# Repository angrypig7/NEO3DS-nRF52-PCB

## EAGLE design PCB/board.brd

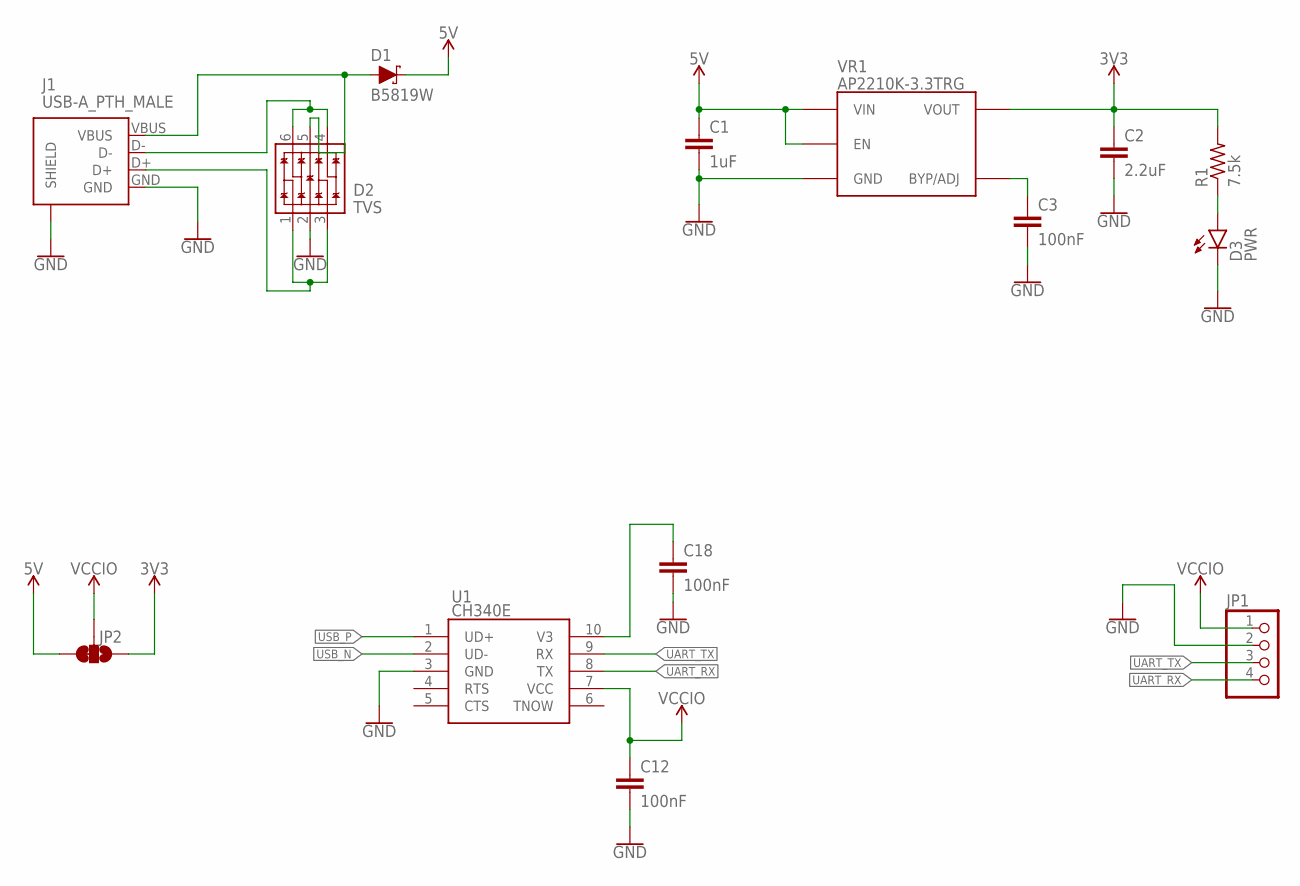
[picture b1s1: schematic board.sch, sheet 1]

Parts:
C1: 1uF; C0402; LCSC C52923
C2: 2.2uF; C0603; LCSC C23630
C3, C12, C18: 100nF; C0402; LCSC C1525
D1: B5819W; SOD-123; LCSC C8598
D2: TVS; SPT-23-6; LCSC C85364
D3: PWR; LED_0603; LCSC C72038
J1: USB-A_PTH_MALE; USB-A-MALE-H-PTH-1; LCSC C9739
JP1: Rx Tx G V; 1X04-NOSILK
JP2: 5V 3V3; SMT-JUMPER_3_1-NC_TRACE_NO-SILK
R1: 7.5k; R0402; LCSC C25918
U1: CH340E; MSOP-10; LCSC C99652
VR1: AP2210K-3.3TRG; SOT-23-5; LCSC C176959

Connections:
3V3: C2.1, JP2.1, R1.2, VR1.5 (VOUT); also elsewhere on the board
5V: C1.1, D1.C, JP2.3, VR1.1 (VIN), VR1.3 (EN)
GND: C1.2, C2.2, C3.2, C12.2, C18.2, D2.2 (VSS), D3.C, J1.GND, J1.SHIELD@0 (SHIELD), J1.SHIELD@1 (SHIELD), J1.SHIELD@2 (SHIELD), J1.SHIELD@3 (SHIELD), JP1.2, U1.3 (GND), VR1.2 (GND); also elsewhere on the board
unnamed: C3.1, VR1.4 (BYP/ADJ)
unnamed: D3.A, R1.1
unnamed: C18.1, U1.10 (V3)
UART_RX: JP1.4, U1.8 (TX); also elsewhere on the board
UART_TX: JP1.3, U1.9 (RX); also elsewhere on the board
USB_IN: D1.A, D2.5 (VCC), J1.VBUS
USB_N: D2.4 (IO3), D2.6 (IO4), J1.D-, U1.2 (UD-)
USB_P: D2.1 (IO1), D2.3 (IO2), J1.D+, U1.1 (UD+)
VCCIO: C12.1, JP1.1, JP2.2, U1.7 (VCC)

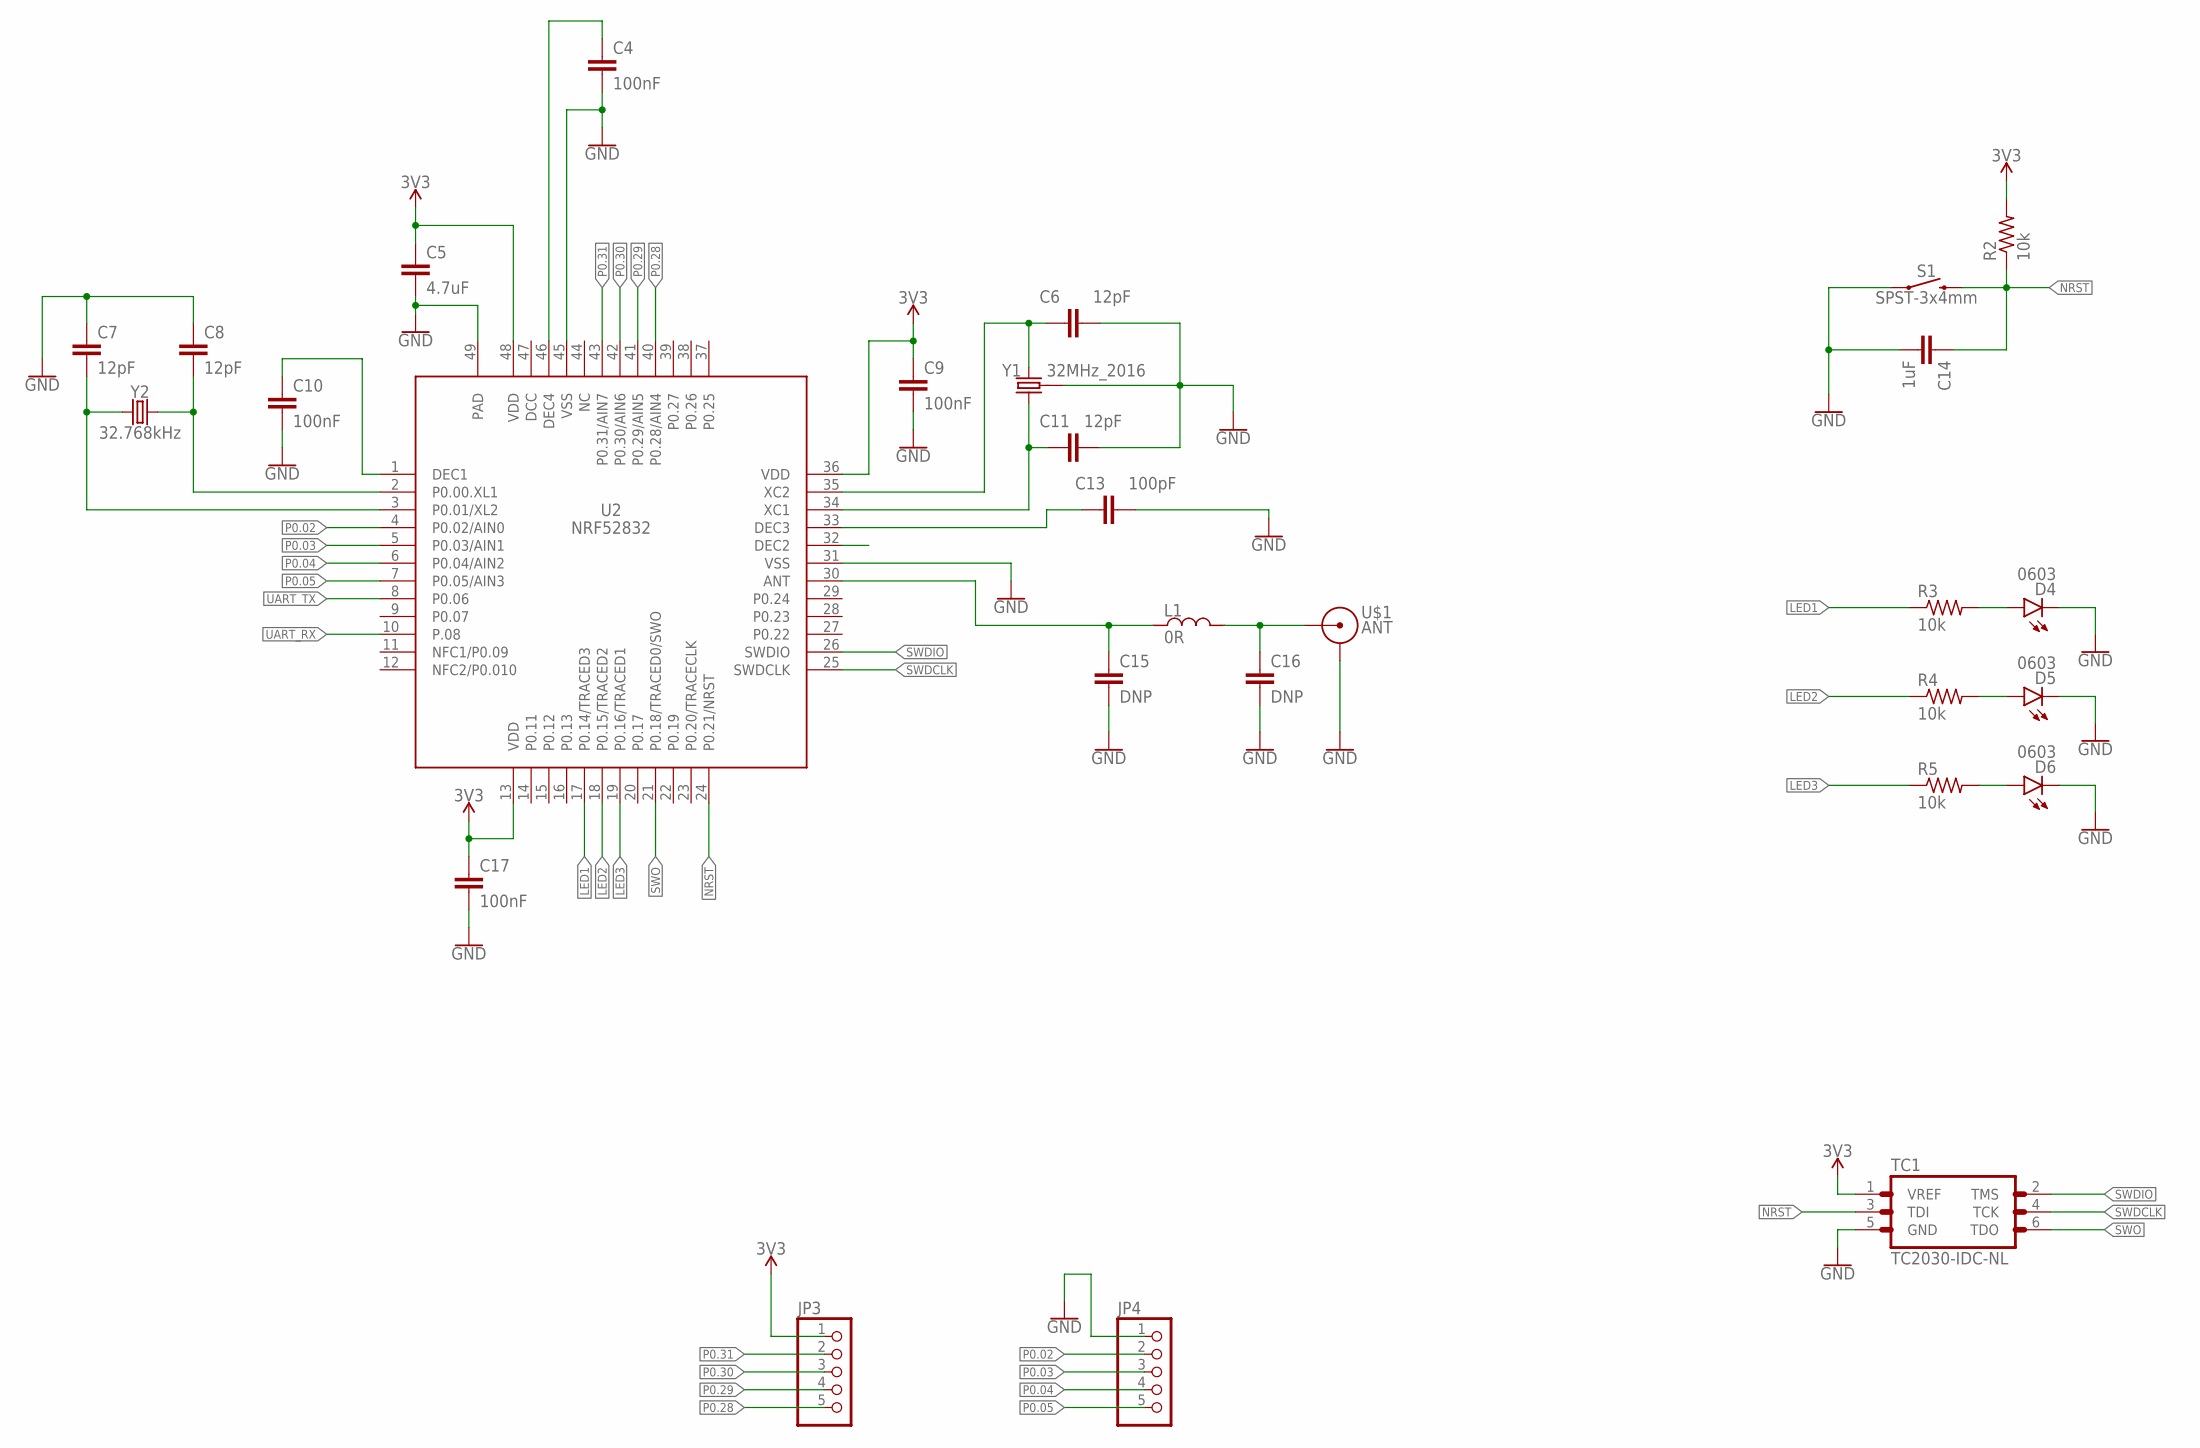
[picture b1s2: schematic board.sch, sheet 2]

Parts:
C4, C9, C10, C17: 100nF; C0402; LCSC C1525
C5: 4.7uF; C0402; LCSC C23733
C6, C7, C8, C11: 12pF; C0402; LCSC C1547
C13: 100pF; C0402; LCSC C1546
C14: 1uF; C0402; LCSC C52923
C15, C16: DNP; C0402
D4, D5, D6: 0603; LED_0603; LCSC C2286
JP3, JP4: PINHD-1X5-NOSILK; 1X05-NOSILK
L1: 0R; R0402; LCSC C17168
R2, R3, R4, R5: 10k; R0402; LCSC C25744
S1: SPST-3x4mm; TACTILE_SWITCH_SMD_3.0X4.0MM; LCSC C720477
TC1: TC2030-IDC-NL
U2: NRF52832; QFN40P600X600X90-49T450N; JLC_ROTATION 270
U$1: ANT; TI-AN043_LEFT_SHORTER
Y1: 32MHz_2016; CRYSTAL-SMD-2.0X1.6MM; LCSC C255896
Y2: 32.768kHz; CRYSTAL-SMD-3.2X1.5MM; LCSC C32346

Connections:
3V3: C5.1, C9.1, C17.1, JP3.1, R2.2, TC1.1 (VREF), U2.13 (VDD), U2.36 (VDD), U2.48 (VDD); also elsewhere on the board
GND: C4.2, C5.2, C6.2, C7.1, C8.1, C9.2, C10.2, C11.2, C13.2, C14.2, C15.2, C16.2, C17.2, D4.C, D5.C, D6.C, JP4.1, S1.1, TC1.5 (GND), U2.31 (VSS), U2.45 (VSS), U2.49 (PAD), U$1.GND, Y1.2 (GND), Y1.4 (GND); also elsewhere on the board
LED1: R3.1, U2.17 (P0.14/TRACED3)
LED2: R4.1, U2.18 (P0.15/TRACED2)
LED3: R5.1, U2.19 (P0.16/TRACED1)
unnamed: C8.2, U2.2 (P0.00.XL1), Y2.P$2 (2)
unnamed: D4.A, R3.2
unnamed: C7.2, U2.3 (P0.01/XL2), Y2.P$1 (1)
unnamed: C10.1, U2.1 (DEC1)
unnamed: C4.1, U2.46 (DEC4)
unnamed: C6.1, U2.35 (XC2), Y1.3 (2)
unnamed: C11.1, U2.34 (XC1), Y1.1
unnamed: C13.1, U2.33 (DEC3)
unnamed: D5.A, R4.2
unnamed: D6.A, R5.2
NRST: C14.1, R2.1, S1.2, TC1.3 (TDI), U2.24 (P0.21/NRST)
P0.02: JP4.2, U2.4 (P0.02/AIN0)
P0.03: JP4.3, U2.5 (P0.03/AIN1)
P0.04: JP4.4, U2.6 (P0.04/AIN2)
P0.05: JP4.5, U2.7 (P0.05/AIN3)
P0.28: JP3.5, U2.40 (P0.28/AIN4)
P0.29: JP3.4, U2.41 (P0.29/AIN5)
P0.30: JP3.3, U2.42 (P0.30/AIN6)
P0.31: JP3.2, U2.43 (P0.31/AIN7)
RF-1: C15.1, L1.1, U2.30 (ANT)
RF-2: C16.1, L1.2, U$1.RF (FEED)
SWDCLK: TC1.4 (TCK), U2.25 (SWDCLK)
SWDIO: TC1.2 (TMS), U2.26 (SWDIO)
SWO: TC1.6 (TDO), U2.21 (P0.18/TRACED0/SWO)
UART_RX: U2.10 (P.08); also elsewhere on the board
UART_TX: U2.8 (P0.06); also elsewhere on the board

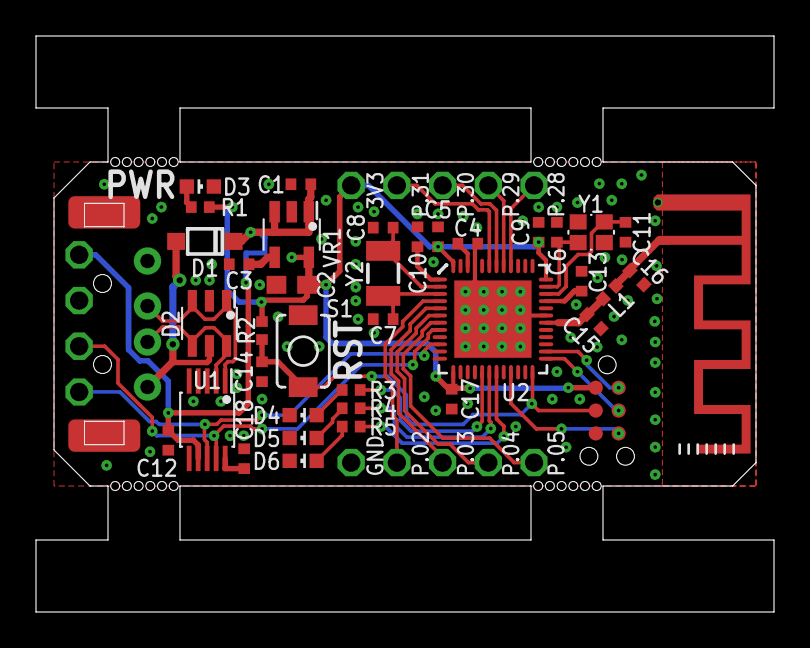
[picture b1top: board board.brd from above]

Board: 2 copper layers, 41.0 x 32.0 mm, 43 parts (1 on the bottom side), 39 nets.

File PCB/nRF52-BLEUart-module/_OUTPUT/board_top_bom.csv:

Comment,Designator,Footprint,LCSC Part #
0R,L1,R0402,C17168
1uF,C1 C14,C0402,C52923
2.2uF,C2,C0603,C23630
4.7uF,C5,C0402,C23733
7.5k,R1,R0402,C25918
10k,R2 R3 R4 R5,R0402,C25744
12pF,C6 C7 C8 C11,C0402,C1547
32.768kHz,Y2,CRYSTAL-SMD-3.2X1.5MM,C32346
32MHz_2016,Y1,CRYSTAL-SMD-2.0X1.6MM,C255896
100nF,C3 C4 C9 C10 C12 C17 C18,C0402,C1525
100pF,C13,C0402,C1546
0603,D4 D5 D6,LED_0603,C2286
ANT,U$1,TI-AN043_LEFT_SHORTER,
AP2210K-3.3TRG,VR1,SOT-23-5,C176959
B5819W,D1,SOD-123,C8598
CH340E,U1,MSOP-10,C99652
DNP,C15 C16,C0402,
NRF52832,U2,QFN40P600X600X90-49T450N,C77540
PWR,D3,LED_0603,C72038
SPST-3x4mm,S1,TACTILE_SWITCH_SMD_3.0X4.0MM,C720477
TC2030-IDC-NL,TC1,TC2030-IDC-NL,
TVS,D2,SPT-23-6,C85364
USB-A_PTH_MALE,J1,USB-A-H-RECT,C98125

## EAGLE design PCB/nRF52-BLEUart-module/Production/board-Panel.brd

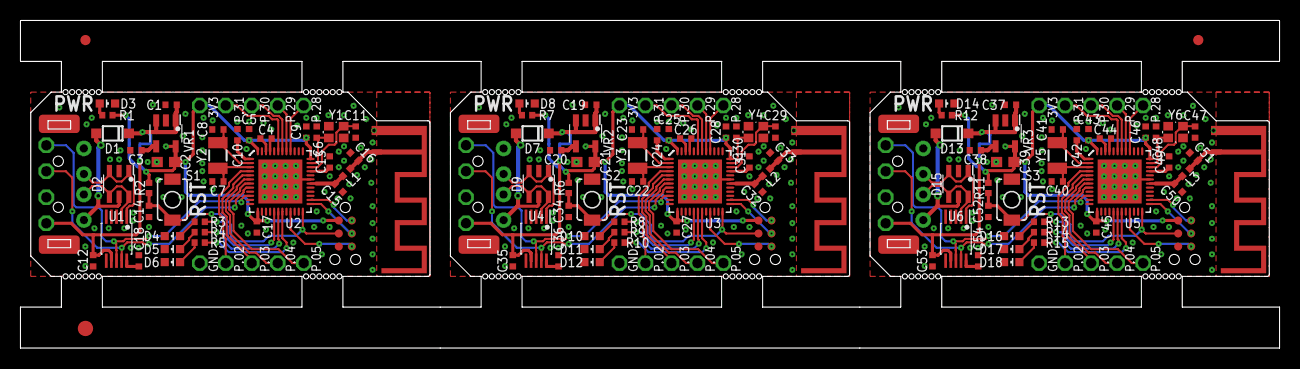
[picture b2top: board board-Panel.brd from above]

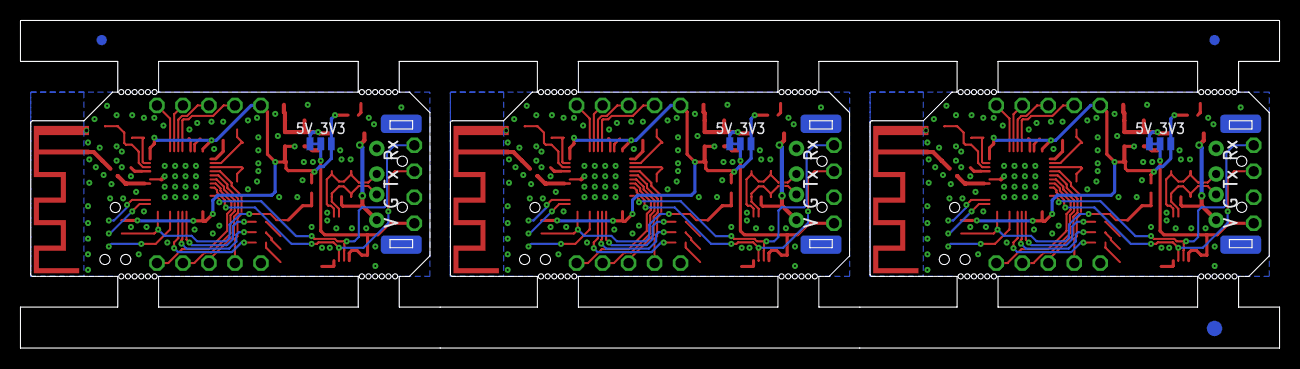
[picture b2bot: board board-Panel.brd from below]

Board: 2 copper layers, 123.0 x 32.0 mm, 135 parts (6 on the bottom side), 117 nets.

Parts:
C1, C14, C19, C34, C37, C52: 1uF; C0402
C2, C21, C39: 2.2uF; C0603
C3, C4, C9, C10, C12, C17, C18, C20, C24, C26, C27, C28, C35, C36, C38, C42, C44, C45, C46, C53, C54: 100nF; C0402
C5, C25, C43: 4.7uF; C0402
C6, C7, C8, C11, C22, C23, C29, C30, C40, C41, C47, C48: 12pF; C0402
C13, C31, C49: 100pF; C0402
C15, C16, C32, C33, C50, C51: DNP; C0402
D1, D7, D13: B5819W; SOD-123
D2, D9, D15: TVS; SPT-23-6
D3, D8, D14: PWR; LED_0603
D4, D5, D6, D10, D11, D12, D16, D17, D18: 0603; LED_0603
E$1, E$2, E$3, E$4: FIDUCIAL-1X2
E$5, E$6: FIDUCIAL-1.5X3
J1, J2, J3: USB-A_PTH_MALE; USB-A-H-RECT
JP1, JP5, JP9: V G Tx Rx; 1X04-NOSILK
JP2, JP6, JP10: 5V 3V3; SMT-JUMPER_3_1-NC_TRACE_NO-SILK
JP3, JP4, JP7, JP8, JP11, JP12: 1X05-NOSILK
L1, L2, L3: 0R; R0402
R1, R7, R12: 15k; R0402
R2, R3, R4, R5, R6, R8, R9, R10, R11, R13, R14, R15: 10k; R0402
S1, S2, S3: SPST-3x4mm; TACTILE_SWITCH_SMD_3.0X4.0MM
TC1, TC2, TC3: TC2030-IDC-NL
U1, U4, U6: CH340E; MSOP-10
U2, U3, U5: NRF52832; QFN40P600X600X90-49T450N
U$1, U$2, U$3: ANT; TI-AN043_LEFT
VR1, VR2, VR3: AP2210K-3.3TRG; SOT-23-5
Y1, Y4, Y6: 32MHz_2016; CRYSTAL-SMD-2.0X1.6MM
Y2, Y3, Y5: 32.768kHz; CRYSTAL-SMD-3.2X1.5MM

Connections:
3V1: C21.1, C25.1, C27.1, C28.1, JP6.1, JP7.1, R6.2, R7.2, TC2.1, U3.13, U3.36, U3.48, VR2.5
3V2: C39.1, C43.1, C45.1, C46.1, JP10.1, JP11.1, R11.2, R12.2, TC3.1, U5.13, U5.36, U5.48, VR3.5
3V3: C2.1, C5.1, C9.1, C17.1, JP2.1, JP3.1, R1.2, R2.2, TC1.1, U2.13, U2.36, U2.48, VR1.5
5V: C1.1, D1.C, JP2.3, VR1.1, VR1.3
5V1: C19.1, D7.C, JP6.3, VR2.1, VR2.3
5V2: C37.1, D13.C, JP10.3, VR3.1, VR3.3
GND: C1.2, C2.2, C3.2, C4.2, C5.2, C6.2, C7.1, C8.1, C9.2, C10.2, C11.2, C12.2, C13.2, C14.2, C15.2, C16.2, C17.2, C18.2, D2.2, D3.C, D4.C, D5.C, D6.C, J1.GND, J1.SHIELD@0, J1.SHIELD@1, J1.SHIELD@2, J1.SHIELD@3, JP1.2, JP4.1, S1.1, TC1.5, U1.3, U2.31, U2.45, U2.49, U$1.GND, VR1.2, Y1.2, Y1.4
GND1: C19.2, C20.2, C21.2, C22.1, C23.1, C24.2, C25.2, C26.2, C27.2, C28.2, C29.2, C30.2, C31.2, C32.2, C33.2, C34.2, C35.2, C36.2, D8.C, D9.2, D10.C, D11.C, D12.C, J2.GND, J2.SHIELD@0, J2.SHIELD@1, J2.SHIELD@2, J2.SHIELD@3, JP5.2, JP8.1, S2.1, TC2.5, U3.31, U3.45, U3.49, U4.3, U$2.GND, VR2.2, Y4.2, Y4.4
GND2: C37.2, C38.2, C39.2, C40.1, C41.1, C42.2, C43.2, C44.2, C45.2, C46.2, C47.2, C48.2, C49.2, C50.2, C51.2, C52.2, C53.2, C54.2, D14.C, D15.2, D16.C, D17.C, D18.C, J3.GND, J3.SHIELD@0, J3.SHIELD@1, J3.SHIELD@2, J3.SHIELD@3, JP9.2, JP12.1, S3.1, TC3.5, U5.31, U5.45, U5.49, U6.3, U$3.GND, VR3.2, Y6.2, Y6.4
LED1: R3.1, U2.17
LED2: R4.1, U2.18
LED3: R5.1, U2.19
LED4: R8.1, U3.17
LED5: R9.1, U3.18
LED6: R10.1, U3.19
LED7: R13.1, U5.17
LED8: R14.1, U5.18
LED9: R15.1, U5.19
unnamed: C8.2, U2.2, Y2.P$2
unnamed: D4.A, R3.2
unnamed: C3.1, VR1.4
unnamed: C7.2, U2.3, Y2.P$1
unnamed: C10.1, U2.1
unnamed: D3.A, R1.1
unnamed: C4.1, U2.46
unnamed: C6.1, U2.35, Y1.3
unnamed: C11.1, U2.34, Y1.1
unnamed: C13.1, U2.33
unnamed: D5.A, R4.2
unnamed: C20.1, VR2.4
unnamed: D6.A, R5.2
unnamed: C23.2, U3.2, Y3.P$2
unnamed: C18.1, U1.10
unnamed: C22.2, U3.3, Y3.P$1
unnamed: C24.1, U3.1
unnamed: C26.1, U3.46
unnamed: C30.1, U3.35, Y4.3
unnamed: C29.1, U3.34, Y4.1
unnamed: C31.1, U3.33
unnamed: D8.A, R7.1
unnamed: C36.1, U4.10
unnamed: D10.A, R8.2
unnamed: D11.A, R9.2
unnamed: D12.A, R10.2
unnamed: C38.1, VR3.4
unnamed: C41.2, U5.2, Y5.P$2
unnamed: C40.2, U5.3, Y5.P$1
unnamed: C42.1, U5.1
unnamed: C44.1, U5.46
unnamed: C48.1, U5.35, Y6.3
unnamed: C47.1, U5.34, Y6.1
unnamed: C49.1, U5.33
unnamed: D14.A, R12.1
unnamed: C54.1, U6.10
unnamed: D16.A, R13.2
unnamed: D17.A, R14.2
unnamed: D18.A, R15.2
NRST: C14.1, R2.1, S1.2, TC1.3, U2.24
NRST1: C34.1, R6.1, S2.2, TC2.3, U3.24
NRST2: C52.1, R11.1, S3.2, TC3.3, U5.24
P0.01: JP8.2, U3.4
P0.02: JP4.2, U2.4
P0.03: JP4.3, U2.5
P0.04: JP4.4, U2.6
P0.05: JP4.5, U2.7
P0.06: JP7.2, U3.43
P0.07: JP7.3, U3.42
P0.08: JP7.4, U3.41
P0.09: JP7.5, U3.40
P0.10: JP8.3, U3.5
P0.11: JP8.4, U3.6
P0.12: JP8.5, U3.7
P0.13: JP12.2, U5.4
P0.14: JP11.2, U5.43
P0.15: JP11.3, U5.42
P0.16: JP11.4, U5.41
P0.17: JP11.5, U5.40
P0.18: JP12.3, U5.5
P0.19: JP12.4, U5.6
P0.20: JP12.5, U5.7
P0.28: JP3.5, U2.40
P0.29: JP3.4, U2.41
P0.30: JP3.3, U2.42
P0.31: JP3.2, U2.43
RF-1: C15.1, L1.1, U2.30
RF-2: C16.1, L1.2, U$1.RF
RF-3: C33.1, L2.2, U$2.RF
RF-4: C32.1, L2.1, U3.30
RF-5: C51.1, L3.2, U$3.RF
RF-6: C50.1, L3.1, U5.30
SWDCLK: TC1.4, U2.25
SWDCLK1: TC2.4, U3.25
SWDCLK2: TC3.4, U5.25
SWDIO: TC1.2, U2.26
SWDIO1: TC2.2, U3.26
SWDIO2: TC3.2, U5.26
SWO: TC1.6, U2.21
SWO1: TC2.6, U3.21
SWO2: TC3.6, U5.21
UART_RX: JP1.4, U1.8, U2.10
UART_RX1: JP5.4, U3.10, U4.8
UART_RX2: JP9.4, U5.10, U6.8
UART_TX: JP1.3, U1.9, U2.8
UART_TX1: JP5.3, U3.8, U4.9
UART_TX2: JP9.3, U5.8, U6.9
USB_IN: D1.A, D2.5, J1.VBUS
USB_IN1: D7.A, D9.5, J2.VBUS
USB_IN2: D13.A, D15.5, J3.VBUS
USB_N: D2.4, D2.6, J1.D-, U1.2
USB_N1: D9.4, D9.6, J2.D-, U4.2
USB_N2: D15.4, D15.6, J3.D-, U6.2
USB_P: D2.1, D2.3, J1.D+, U1.1
USB_P1: D9.1, D9.3, J2.D+, U4.1
USB_P2: D15.1, D15.3, J3.D+, U6.1
VCCIO: C12.1, JP1.1, JP2.2, U1.7
VCCIO1: C35.1, JP5.1, JP6.2, U4.7
VCCIO2: C53.1, JP9.1, JP10.2, U6.7

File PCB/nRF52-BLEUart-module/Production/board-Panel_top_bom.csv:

Comment,Designator,Footprint,LCSC Part #
0R,E$1 E$3 E$5 L1 L2 L3,R0402,C17168
1uF,C1 C14 C19 C34 C37 C52,C0402,C52923
2.2uF,C2 C21 C39,C0603,C23630
4.7uF,C5 C25 C43,C0402,C23733
10k,R2 R3 R4 R5 R6 R8 R9 R10 R11 R13 R14 R15,R0402,C25744
12pF,C6 C7 C8 C11 C22 C23 C29 C30 C40 C41 C47 C48,C0402,C1547
15k,R1 R7 R12,R0402,C25756
32.768kHz,Y2 Y3 Y5,CRYSTAL-SMD-3.2X1.5MM,C32346
32MHz_2016,Y1 Y4 Y6,CRYSTAL-SMD-2.0X1.6MM,C255896
100nF,C3 C4 C9 C10 C12 C17 C18 C20 C24 C26 C27 C28 C35 C36 C38 C42 C44 C45 C46 C53 C54,C0402,C1525
100pF,C13 C31 C49,C0402,C1546
0603,D4 D5 D6 D10 D11 D12 D16 D17 D18,LED_0603,C2286
ANT,U$1 U$2 U$3,TI-AN043_LEFT,
AP2210K-3.3TRG,VR1 VR2 VR3,SOT-23-5,C176959
B5819W,D1 D7 D13,SOD-123,C8598
CH340E,U1 U4 U6,MSOP-10,C99652
DNP,C15 C16 C32 C33 C50 C51,C0402,
NRF52832,U2 U3 U5,QFN40P600X600X90-49T450N,C77540
PWR,D3 D8 D14,LED_0603,C72038
SPST-3x4mm,S1 S2 S3,TACTILE_SWITCH_SMD_3.0X4.0MM,C720477
TC2030-IDC-NL,TC1 TC2 TC3,TC2030-IDC-NL,
TVS,D2 D9 D15,SPT-23-6,C85364
USB-A_PTH_MALE,J1 J2 J3,USB-A-H-RECT,C98125

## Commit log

2021-01-06 gitignore
2021-01-06 PCB files
2021-01-06 docs
2021-01-06 seperated nRF52832 docs
2021-01-06 PCB update
2021-01-11 PCB update with inverted F antenna
2021-01-13 artwork partially done, layout update
2021-01-13 finished PCB artwork
2021-01-13 fixed serial IO voltage, added GPIO silk
2021-01-13 PCB bug fixes, added production files
2021-01-18 added pics
2021-01-31 fixed #4
2021-01-31 fixed #2, removed unecessary power test pad
2021-01-31 added edge rails, mousebites to the PCB. DRC error fixes needed
2021-02-01 PCB artwork, gerbers and production files - part rotation needs fixes
2021-02-01 final PCB for V1.0
2021-02-17 V1.1.0 update
2021-02-24 output files, dir cleanup
2021-02-26 airwire error fix
2021-02-26 V1.1.0 output files
2021-03-02 pics
2021-03-05 fixed #7, replaced USB connector part.# on BOM
2021-03-27 RF test report
2021-05-04 PCB trace width DFM

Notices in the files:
parts and their libraries:
SparkFun-Aesthetics: Licensing: Creative Commons ShareAlike 4.0 International - https://creativecommons.org/licenses/by-sa/4.0
